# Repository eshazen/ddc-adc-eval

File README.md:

# ddc-adc-eval

Evaluation board for DDC112 ADC (Arduino UNO shield?).
See `led-photodiode-avr` design for working board.

## Notes from DDC112 datasheet:

* CLK freq range 1-10MHz
* Can generate 8MHz easily using AVR CTC
  <br>Conversion rate then 1.6kHz max
* It is recommended CONV toggle within ±10ns of the rising edge of CLK
* Mode (Cont vs Ncont) selected by state of CONT pin at power-up
  <br>can also switch based on T(INT): space between CONV edges > 4794 clocks
  (600uS at 8MHz clock)
* Data ready at ~526uS at 8MHz (4208 clocks)

## Readout strategy

* Readout function takes ~32us for 20 bits
* So maybe use CONV period of 558 + 10us (568us or 4544 clocks - 9088 period)

## Version 2 ECOs

### Main board

* **Address conflict** - U1 and U5 have the same address.
<br>Need to cut trace to U5-13 and wire U15-13 to U15-16
<br>This changes U5 address from 0x90 to 0x92
* [done] Add transistors, expand to support 8 LEDs
* [done] Change to common anode configuration (incl connector pinout)
* [done] Correct external caps on DDC (2 -> 4 C's)
* [done] Add 12 bit ADC for temperature sensor
* [done] Testpoints?

### Optical board

* [done] Fix photodiode pinout
* [done] Add temp sensor next to photodiode on copper pad
* [done] Add two Marubeni footprints next to D1 and D3
* [done] Wire 8 LED drivers to the 9 LEDs with a jumper to choose between e.g. D3 and one Marubeni channel.
* [done] Change to common anode topology
*

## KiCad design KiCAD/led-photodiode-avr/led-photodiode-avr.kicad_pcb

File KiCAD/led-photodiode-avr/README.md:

# led-photodiode-avr

This is a test board with a 3-channel constant-current LED driver,
two-channel DDC112 ADC and an ATMega328 MCU.

An interactive CLI for testing is available in
`software/avr-clock-test`.

## Testing

Board#1 is in Lina's hands

Board#2 stuffing

* C1, C15 MIA so installed 0.47uF in place of 0.33uF

Running now.

T = 9800 works well

## ECOs

Rev 2 layout completed.  See top-level README for change details.

DigiKey card for (3) sets:  https://www.digikey.com/short/bnw3t94d

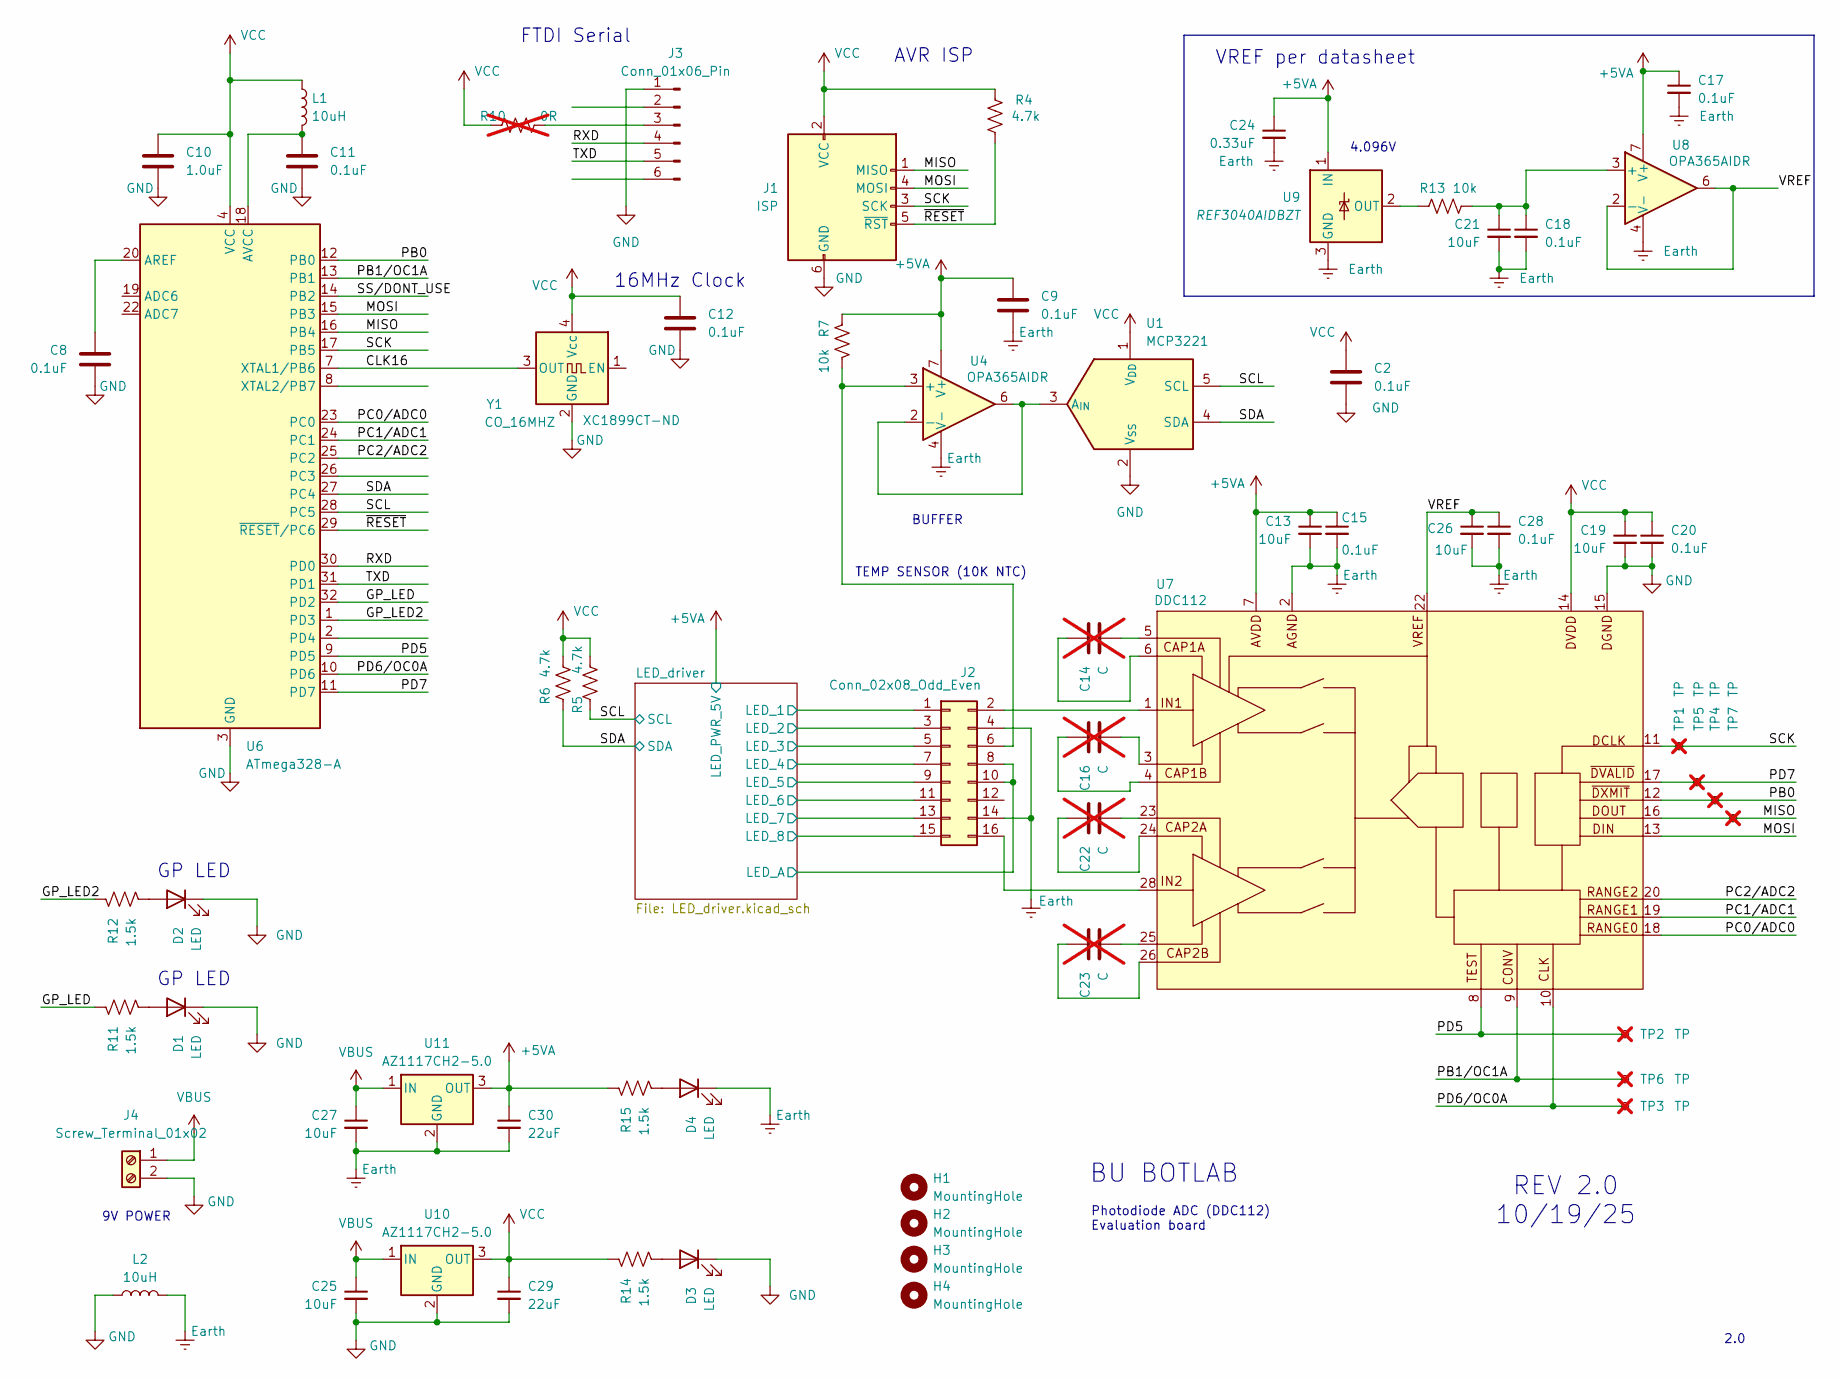
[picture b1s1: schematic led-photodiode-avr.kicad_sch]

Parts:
C2, C8, C9, C11, C12, C15, C17, C18, C20, C28: 0.1uF; C_0805_2012Metric_Pad1.18x1.45mm_HandSolder; DigikeyNumber 478-KGM21NR71H104KTCT-ND
C10: 1.0uF; C_0805_2012Metric_Pad1.18x1.45mm_HandSolder; DigikeyNumber 1276-1029-1-ND
C13, C19, C21, C25, C26, C27: 10uF; C_0805_2012Metric_Pad1.18x1.45mm_HandSolder; DigikeyNumber 1292-0805X106K250CT-ND
C14, C16, C22, C23: C; C_0603_1608Metric_Pad1.08x0.95mm_HandSolder; not fitted
C24: 0.33uF; C_0805_2012Metric_Pad1.18x1.45mm_HandSolder; DigikeyNumber 1276-1123-1-ND
C29, C30: 22uF; C_0805_2012Metric_Pad1.18x1.45mm_HandSolder; DigikeyNumber 1276-CL21A226MAYNNNECT-ND
D1, D2, D3, D4: LED; LED_0805_2012Metric_Pad1.15x1.40mm_HandSolder; DigikeyNumber 1516-QBLP631-R3ACT-ND
H1, H2, H3, H4: MountingHole; MountingHole_4.3mm_M4_DIN965_Pad
J1: ISP; IDC-Header_2x03_P2.54mm_Horizontal; DigikeyNumber 952-2092-ND
J2: Conn_02x08_Odd_Even; PinHeader_2x08_P2.54mm_Vertical; DigikeyNumber 10129381-916001BLF-ND
J3: Conn_01x06_Pin; PinHeader_1x06_P2.54mm_Horizontal; DigikeyNumber 2057-PH1RB-06-UA-ND
J4: Screw_Terminal_01x02; TerminalBlock_MaiXu_MX126-5.0-02P_1x02_P5.00mm; DigikeyNumber A98076-ND
L1, L2: 10uH; L_0805_2012Metric_Pad1.15x1.40mm_HandSolder; DigikeyNumber 445-6762-1-ND
R4, R5, R6: 4.7k; R_0805_2012Metric_Pad1.20x1.40mm_HandSolder; DigikeyNumber 541-4131-1-ND
R7, R13: 10k; R_0805_2012Metric_Pad1.20x1.40mm_HandSolder; DigikeyNumber P10KACT-ND
R10: 0R; R_0805_2012Metric_Pad1.20x1.40mm_HandSolder; not fitted
R11, R12, R14, R15: 1.5k; R_0805_2012Metric_Pad1.20x1.40mm_HandSolder; DigikeyNumber 541-4161-1-ND
TP1, TP2, TP3, TP4, TP5, TP6, TP7: TP; TestPoint_Pad_D1.0mm; not fitted
U1: MCP3221; SOT-23-5; DigikeyNumber MCP3221A0T-E/OTCT-ND
U4, U8: OPA365AIDR; SOIC-8_3.9x4.9mm_P1.27mm; DigikeyNumber 296-46162-1-ND
U6: ATmega328-A; TQFP-32_7x7mm_P0.8mm; DigikeyNumber ATMEGA328P-AU-ND
U7: DDC112; SOIC-28W_7.5x17.9mm_P1.27mm; DigikeyNumber 296-DDC112U/1KCT-ND
U9: REF3040AIDBZT; SOT-23; DigikeyNumber REF3040AIDBZTCT-ND
U10, U11: AZ1117CH2-5.0; SOT-223-3_TabPin2; DigikeyNumber 31-AZ1117CH2-5.0TRG1CT-ND
Y1: CO_16MHZ; Oscillator_SMD_Abracon_ASE-4Pin_3.2x2.5mm; DigikeyNumber XC1899CT-ND

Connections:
+5VA: C9.1, C13.1, C15.1, C17.1, C24.1, C30.1, J2.8, J2.10, R7.1, R15.1, U4.7 (V+), U7.7 (AVDD), U8.7 (V+), U9.1 (IN), U11.3 (OUT); also elsewhere on the board
/CLK16: U6.7 (XTAL1/PB6), Y1.3 (OUT)
/GP_LED: R11.1, U6.32 (PD2)
/GP_LED2: R12.1, U6.1 (PD3)
/LED_driver/LED_1: J2.1; also elsewhere on the board
/LED_driver/LED_2: J2.3; also elsewhere on the board
/LED_driver/LED_3: J2.5; also elsewhere on the board
/LED_driver/LED_4: J2.7; also elsewhere on the board
/LED_driver/LED_5: J2.9; also elsewhere on the board
/LED_driver/LED_6: J2.11; also elsewhere on the board
/LED_driver/LED_7: J2.13; also elsewhere on the board
/LED_driver/LED_8: J2.15; also elsewhere on the board
/MISO: J1.1 (MISO), TP7.1, U6.16 (PB4), U7.16 (DOUT)
/MOSI: J1.4 (MOSI), U6.15 (PB3), U7.13 (DIN)
/PB0: TP4.1, U6.12 (PB0), U7.12 (~DXMIT)
/PB1/OC1A: TP6.1, U6.13 (PB1), U7.9 (CONV)
/PC0/ADC0: U6.23 (PC0), U7.18 (RANGE0)
/PC1/ADC1: U6.24 (PC1), U7.19 (RANGE1)
/PC2/ADC2: U6.25 (PC2), U7.20 (RANGE2)
/PD5: TP2.1, U6.9 (PD5), U7.8 (TEST)
/PD6/OC0A: TP3.1, U6.10 (PD6), U7.10 (CLK)
/PD7: TP5.1, U6.11 (PD7), U7.17 (~DVALID)
/RXD: J3.4, U6.30 (PD0)
/SCK: J1.3 (SCK), TP1.1, U6.17 (PB5), U7.11 (DCLK)
/SCL: R5.1, U1.5 (SCL), U6.28 (PC5); also elsewhere on the board
/SDA: R6.1, U1.4 (SDA), U6.27 (PC4); also elsewhere on the board
/SS/DONT_USE: U6.14 (PB2)
/TXD: J3.5, U6.31 (PD1)
/VREF: C26.1, C28.1, U7.22 (VREF), U8.2 (-), U8.6
/~RESET: J1.5 (~RST), R4.1, U6.29 (~RESET/PC6)
Earth: C9.2, C13.2, C15.2, C17.2, C18.2, C21.2, C24.2, C26.2, C27.2, C28.2, C30.2, D4.1 (K), J2.4, J2.14, L2.2, U4.4 (V-), U7.2 (AGND), U7.21 (AGND), U7.27 (AGND), U8.4 (V-), U9.3 (GND), U11.2 (GND); also elsewhere on the board
GND: C2.2, C8.2, C10.2, C11.2, C12.2, C19.2, C20.2, C25.2, C29.2, D1.1 (K), D2.1 (K), D3.1 (K), J1.6 (GND), J3.1, J4.2, L2.1, U1.2 (V_{SS}), U6.3 (GND), U6.5 (GND), U6.21 (GND), U7.15 (DGND), U10.2 (GND), Y1.2 (GND); also elsewhere on the board
unnamed: C14.1, U7.6 (CAP1A)
unnamed: C14.2, U7.5 (CAP1A)
unnamed: C16.1, U7.4 (CAP1B)
unnamed: C16.2, U7.3 (CAP1B)
unnamed: C22.1, U7.24 (CAP2A)
unnamed: C22.2, U7.23 (CAP2A)
unnamed: C23.1, U7.26 (CAP2B)
unnamed: C23.2, U7.25 (CAP2B)
unnamed: D1.2 (A), R11.2
unnamed: D2.2 (A), R12.2
unnamed: D3.2 (A), R14.2
unnamed: D4.2 (A), R15.2
unnamed: J2.2, U7.1 (IN1)
unnamed: J2.6, R7.2, U4.3 (+)
unnamed: J2.16, U7.28 (IN2)
unnamed: J3.3, R10.2
unnamed: U1.3 (A_{IN}), U4.2 (-), U4.6
unnamed: C8.1, U6.20 (AREF)
unnamed: C11.1, L1.2, U6.18 (AVCC)
unnamed: C18.1, C21.1, R13.2, U8.3 (+)
unnamed: R13.1, U9.2 (OUT)
VBUS: C25.1, C27.1, J4.1, U10.1 (IN), U11.1 (IN)
VCC: C2.1, C10.1, C12.1, C19.1, C20.1, C29.1, J1.2 (VCC), L1.1, R4.2, R5.2, R6.2, R10.1, R14.1, U1.1 (V_{DD}), U6.4 (VCC), U6.6 (VCC), U7.14 (DVDD), U10.3 (OUT), Y1.4 (Vcc); also elsewhere on the board

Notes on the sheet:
BUFFER
REV 2.0 10/19/25
AVR ISP
FTDI Serial
4.096V
2.0
GP LED
VREF per datasheet
9V POWER
BU BOTLAB
TEMP SENSOR (10K NTC)
16MHz Clock
Photodiode ADC (DDC112) Evaluation board

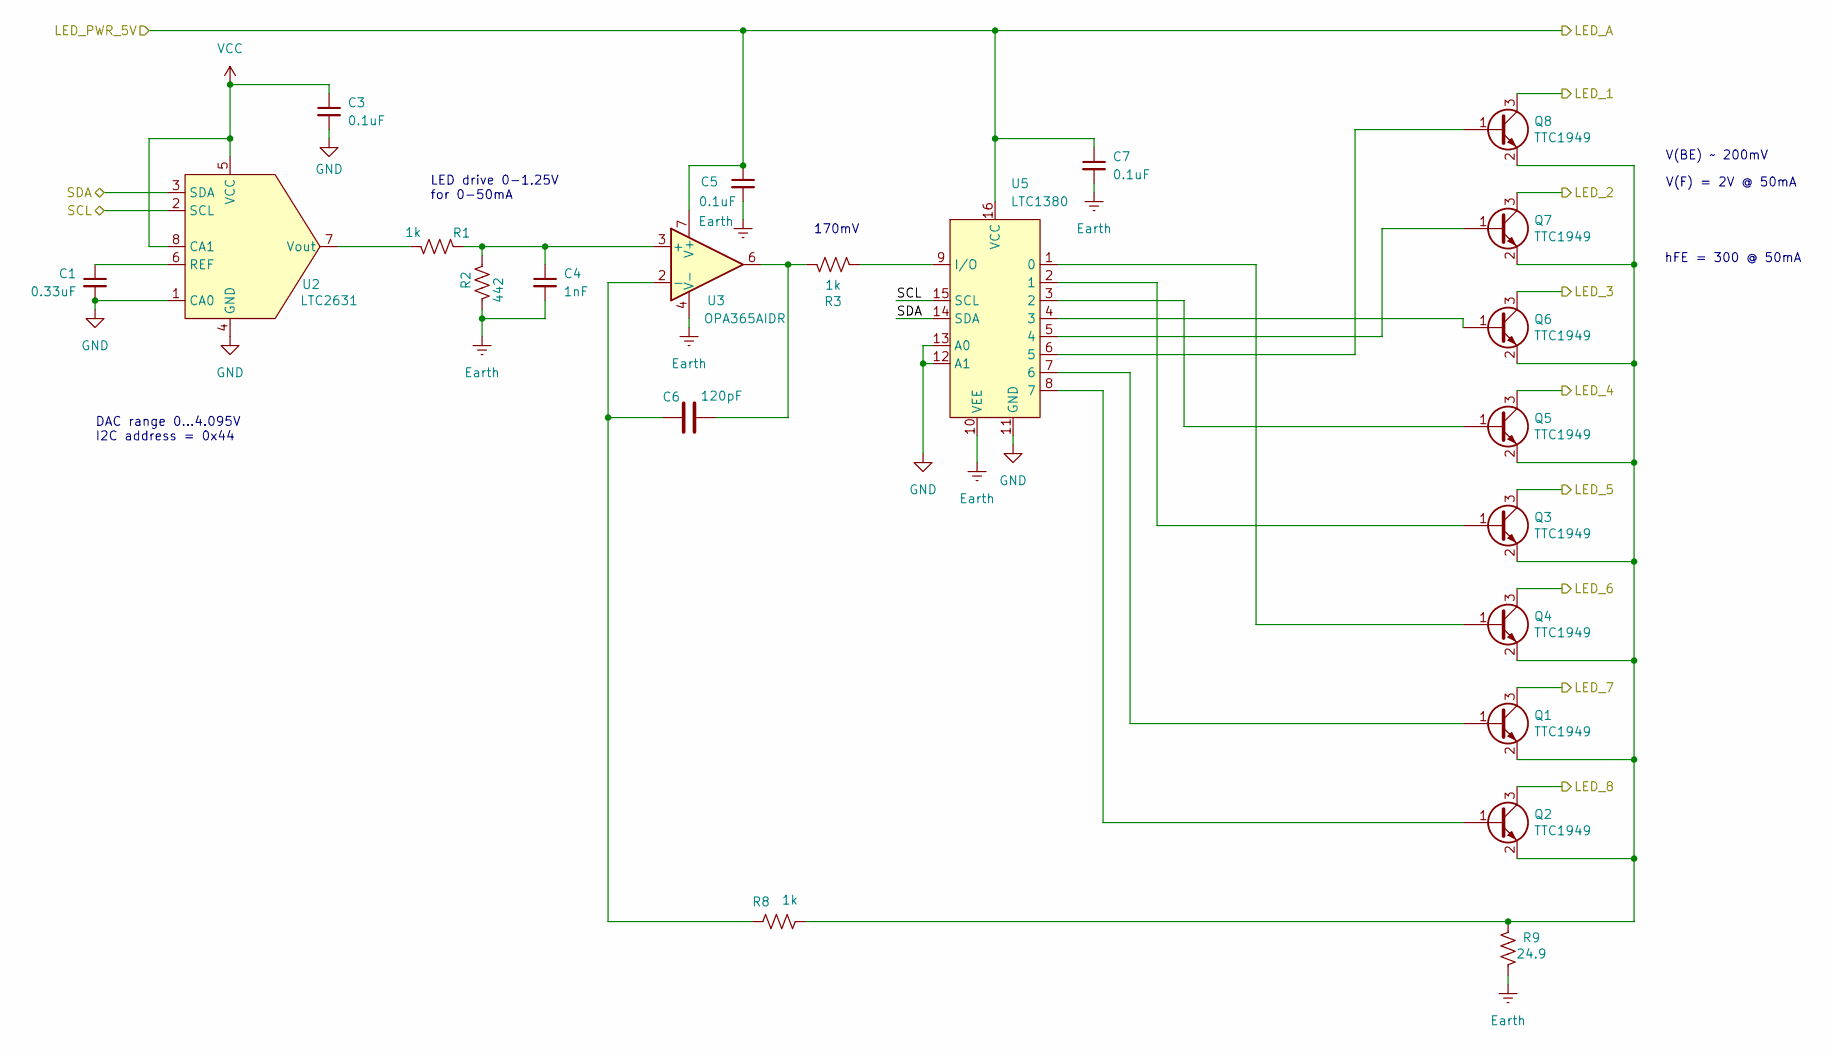
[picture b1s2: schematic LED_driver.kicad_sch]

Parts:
C1: 0.33uF; C_0805_2012Metric_Pad1.18x1.45mm_HandSolder; DigikeyNumber 1276-1123-1-ND
C3, C5, C7: 0.1uF; C_0805_2012Metric_Pad1.18x1.45mm_HandSolder; DigikeyNumber 478-KGM21NR71H104KTCT-ND
C4: 1nF; C_0805_2012Metric_Pad1.18x1.45mm_HandSolder; DigikeyNumber 399-C0805C102J5GACTUCT-ND
C6: 120pF; C_0805_2012Metric_Pad1.18x1.45mm_HandSolder; DigikeyNumber 399-C0805C121J3GACTUCT-ND
Q1, Q2, Q3, Q4, Q5, Q6, Q7, Q8: TTC1949; SC-59; DigikeyNumber TTC1949-GRLFCT-ND
R1, R3, R8: 1k; R_0805_2012Metric_Pad1.20x1.40mm_HandSolder; DigikeyNumber 541-1.00KCCT-ND
R2: 442; R_0805_2012Metric_Pad1.20x1.40mm_HandSolder; DigikeyNumber 311-442CRCT-ND
R9: 24.9; R_1206_3216Metric; DigikeyNumber 541-CRCW120624R9FKEAHPCT-ND
U2: LTC2631; TSOT-23-8; DigikeyNumber LTC2631CTS8-HZ12#TRMPBFCT-ND
U3: OPA365AIDR; SOIC-8_3.9x4.9mm_P1.27mm; DigikeyNumber 296-46162-1-ND
U5: LTC1380; SOIC-16_3.9x9.9mm_P1.27mm; DigikeyNumber 505-LTC1380CS#PBF-ND

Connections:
+5VA: C5.1, C7.1, U3.7 (V+), U5.16 (VCC); also elsewhere on the board
/LED_driver/LED_1: Q8.3 (C); also elsewhere on the board
/LED_driver/LED_2: Q7.3 (C); also elsewhere on the board
/LED_driver/LED_3: Q6.3 (C); also elsewhere on the board
/LED_driver/LED_4: Q5.3 (C); also elsewhere on the board
/LED_driver/LED_5: Q3.3 (C); also elsewhere on the board
/LED_driver/LED_6: Q4.3 (C); also elsewhere on the board
/LED_driver/LED_7: Q1.3 (C); also elsewhere on the board
/LED_driver/LED_8: Q2.3 (C); also elsewhere on the board
/SCL: U2.2 (SCL), U5.15 (SCL); also elsewhere on the board
/SDA: U2.3 (SDA), U5.14 (SDA); also elsewhere on the board
Earth: C4.2, C5.2, C7.2, R2.2, R9.1, U3.4 (V-), U5.10 (VEE); also elsewhere on the board
GND: C1.2, C3.2, U2.1 (CA0), U2.4 (GND), U5.11 (GND), U5.12 (A1), U5.13 (A0); also elsewhere on the board
unnamed: C6.2, R3.2, U3.6
unnamed: Q1.1 (B), U5.7 (6)
unnamed: Q1.2 (E), Q2.2 (E), Q3.2 (E), Q4.2 (E), Q5.2 (E), Q6.2 (E), Q7.2 (E), Q8.2 (E), R8.1, R9.2
unnamed: Q2.1 (B), U5.8 (7)
unnamed: Q3.1 (B), U5.2 (1)
unnamed: Q4.1 (B), U5.1 (0)
unnamed: Q5.1 (B), U5.3 (2)
unnamed: Q6.1 (B), U5.4 (3)
unnamed: Q7.1 (B), U5.5 (4)
unnamed: Q8.1 (B), U5.6 (5)
unnamed: C1.1, U2.6 (REF)
unnamed: R1.2, U2.7 (Vout)
unnamed: C4.1, R1.1, R2.1, U3.3 (+)
unnamed: C6.1, R8.2, U3.2 (-)
unnamed: R3.1, U5.9 (I/O)
VCC: C3.1, U2.5 (VCC), U2.8 (CA1); also elsewhere on the board

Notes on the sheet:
DAC range 0...4.095V I2C address = 0x44
LED drive 0-1.25V for 0-50mA
V(BE) ~ 200mV
170mV
V(F) = 2V @ 50mA
hFE = 300 @ 50mA

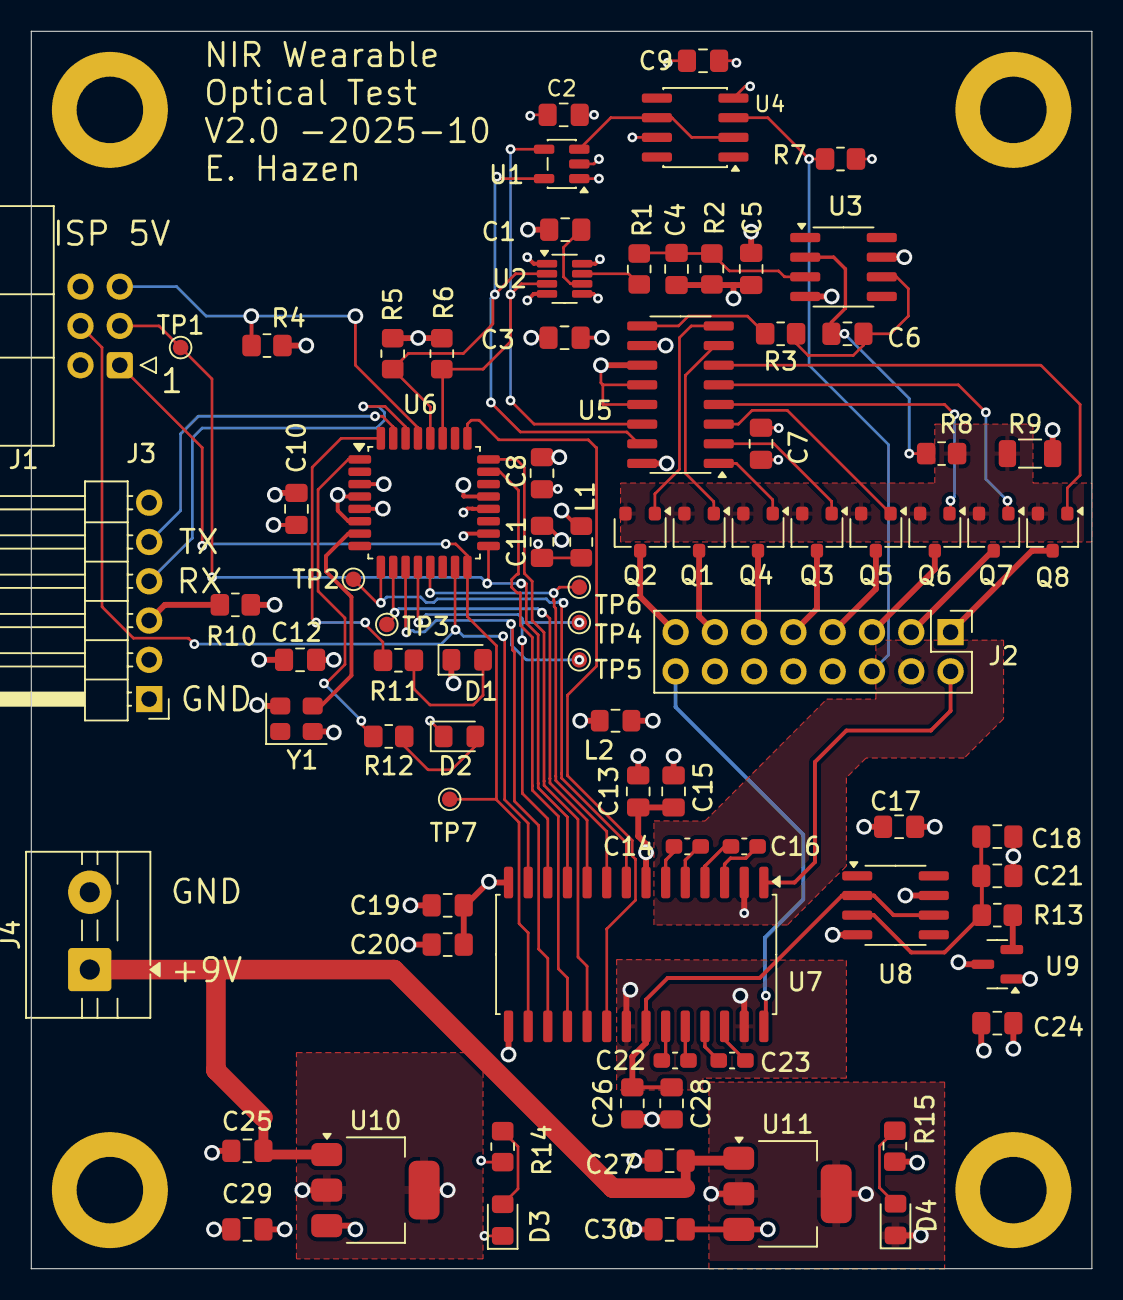
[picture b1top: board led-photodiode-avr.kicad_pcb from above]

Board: 4 copper layers, 68.6 x 80.0 mm, 86 parts (0 on the bottom side), 69 nets.

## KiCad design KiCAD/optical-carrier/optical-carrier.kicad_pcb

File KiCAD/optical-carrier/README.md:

# optical-carrier

Simple carrier board for one photodiode, 3 discrete
and two 3-wavelength LEDs.

## ECOs

Rev 2 layout completed.  See top-level README for details.

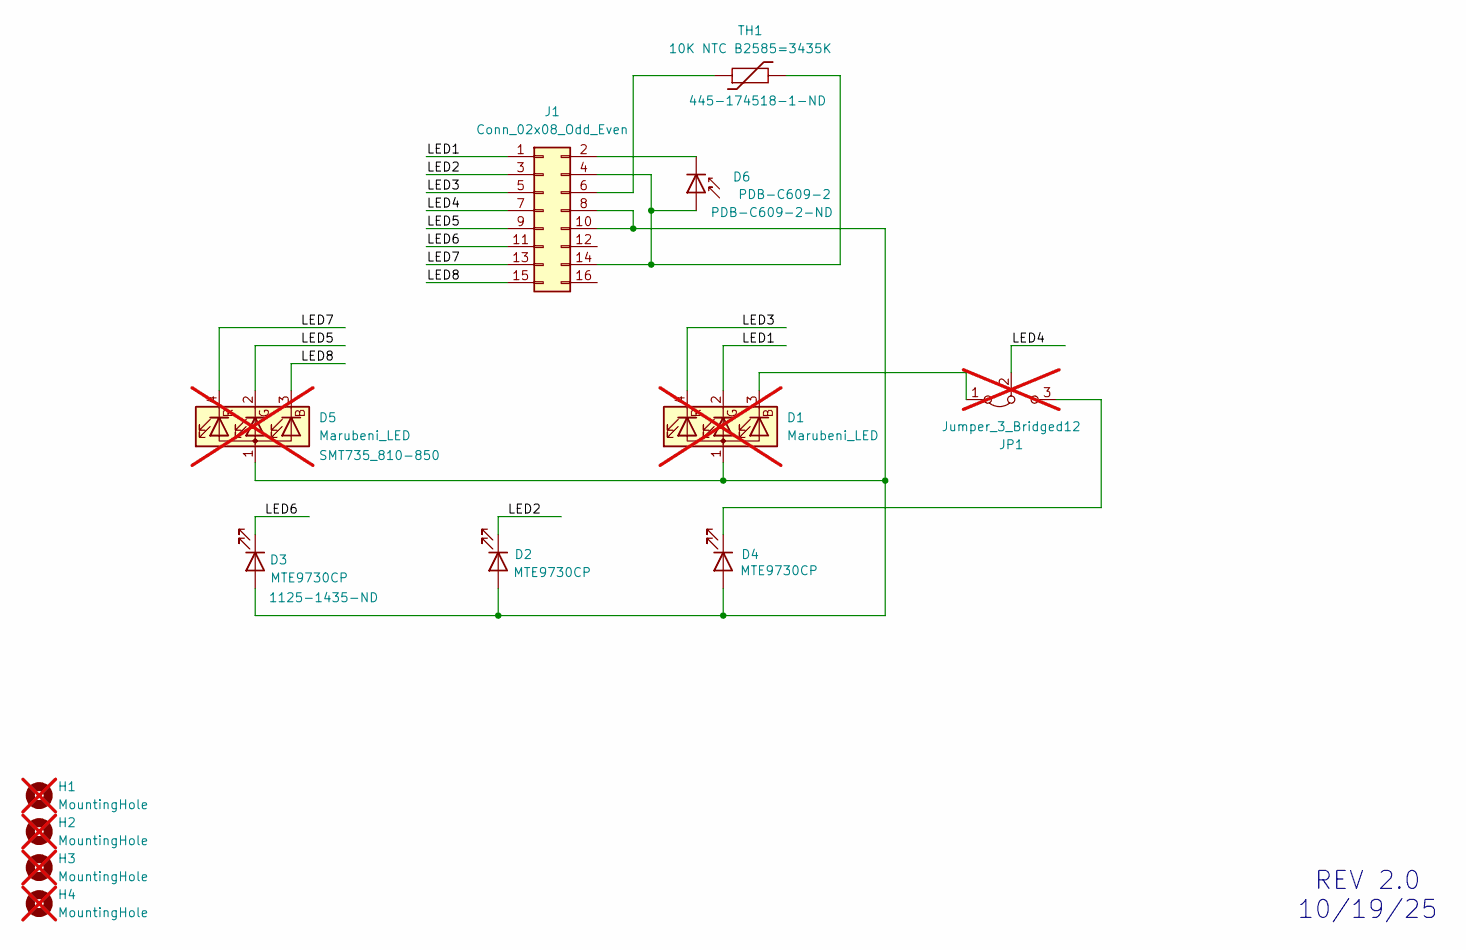
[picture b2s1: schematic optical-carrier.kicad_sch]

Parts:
D1, D5: Marubeni_LED; Marubeni; not fitted
D2, D3, D4: MTE9730CP; MTE9730
D6: PDB-C609-2
H1, H2, H3, H4: MountingHole; MountingHole_4.3mm_M4_DIN965; not fitted
J1: Conn_02x08_Odd_Even; PinSocket_2x08_P2.54mm_Vertical
JP1: Jumper_3_Bridged12; PinHeader_1x03_P2.54mm_Vertical; not fitted
TH1: 10K NTC B2585=3435K; R_0603_1608Metric_Pad0.98x0.95mm_HandSolder

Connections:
/LED1: D1.2 (GK), J1.1
/LED2: D2.1 (K), J1.3
/LED3: D1.4 (RK), J1.5
/LED4: J1.7, JP1.2 (C)
/LED5: D5.2 (GK), J1.9
/LED6: D3.1 (K), J1.11
/LED7: D5.4 (RK), J1.13
/LED8: D5.3 (BK), J1.15
unnamed: D1.1 (A), D2.2 (A), D3.2 (A), D4.2 (A), D5.1 (A), J1.8, J1.10
unnamed: D1.3 (BK), JP1.1 (A)
unnamed: D4.1 (K), JP1.3 (B)
unnamed: D6.2 (A), J1.4, J1.14, TH1.2
unnamed: D6.1 (K), J1.2
unnamed: J1.6, TH1.1

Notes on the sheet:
REV 2.0 10/19/25

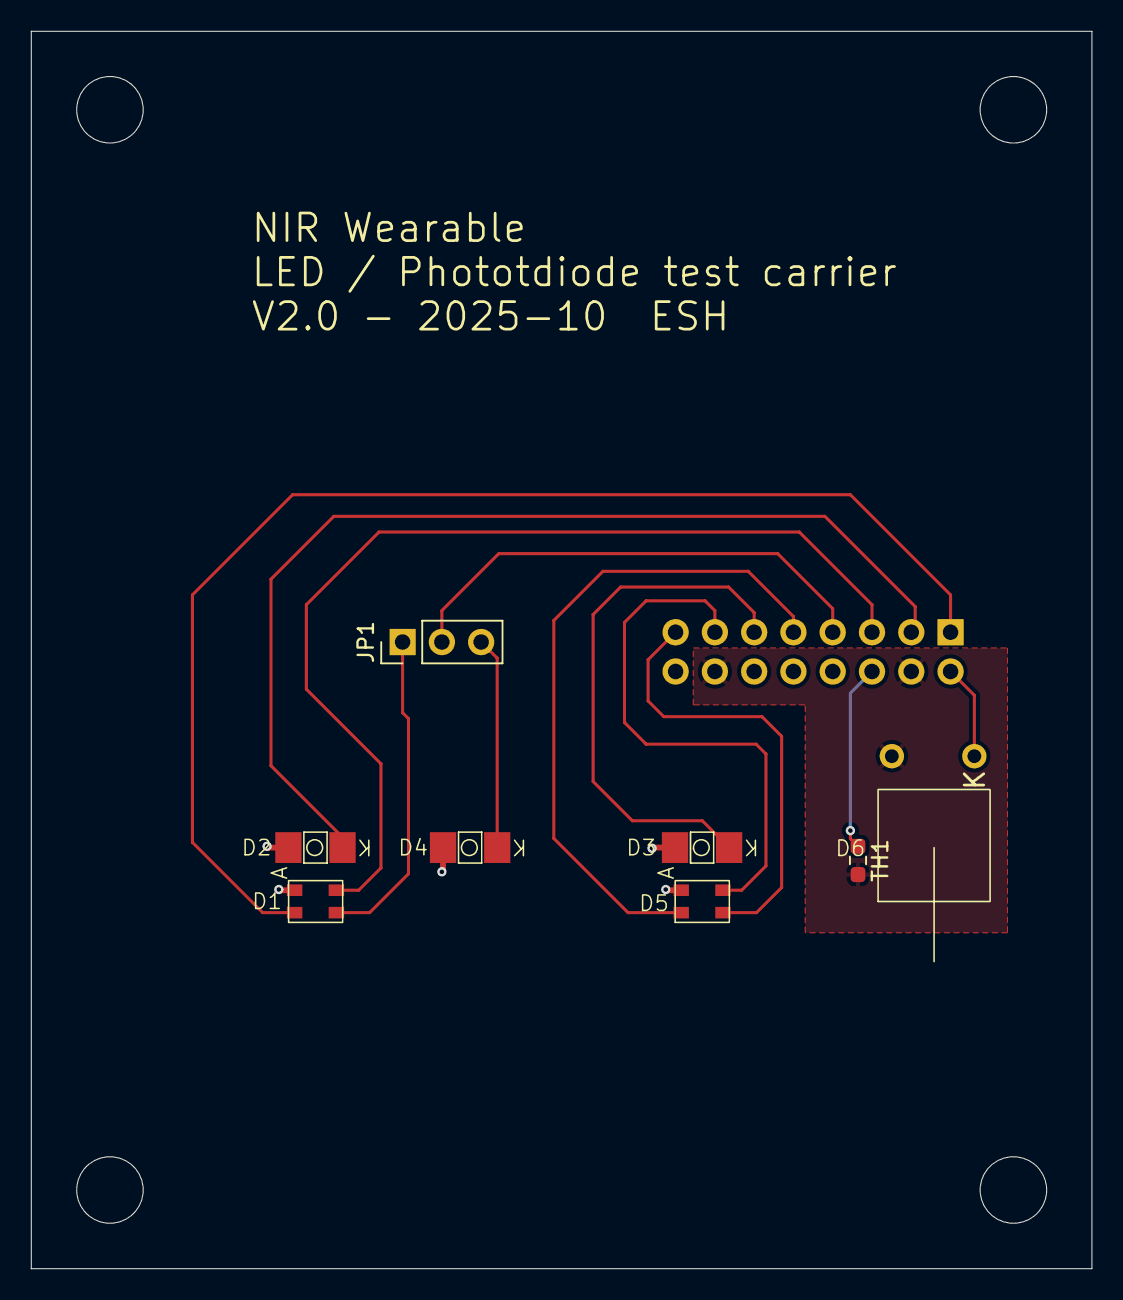
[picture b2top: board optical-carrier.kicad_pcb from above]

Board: 2 copper layers, 68.6 x 80.0 mm, 13 parts (1 on the bottom side), 14 nets.

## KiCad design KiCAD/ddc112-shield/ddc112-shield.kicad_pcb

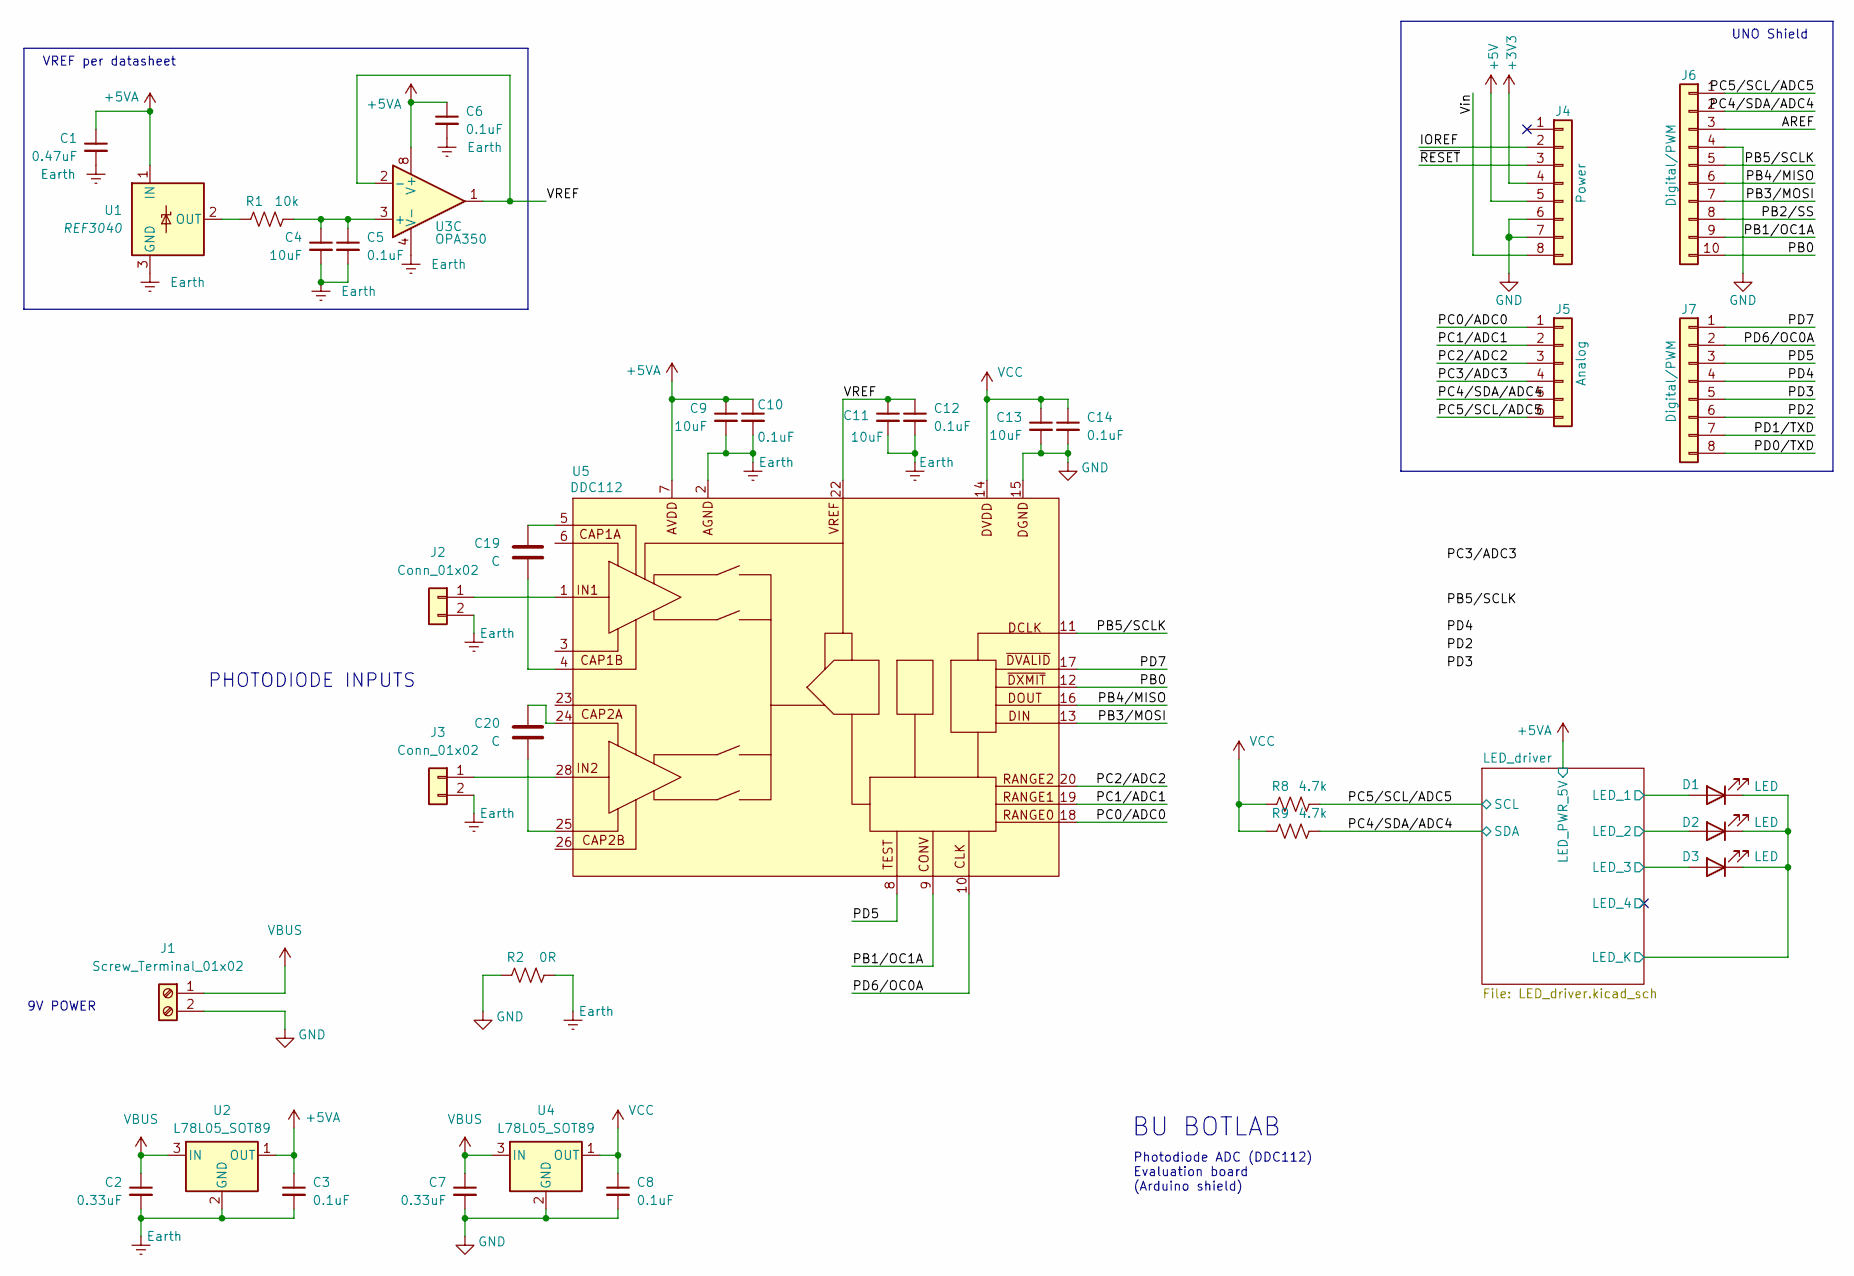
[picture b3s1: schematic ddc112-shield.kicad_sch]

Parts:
C1: 0.47uF; C_0805_2012Metric_Pad1.18x1.45mm_HandSolder
C2, C7: 0.33uF; C_0805_2012Metric_Pad1.18x1.45mm_HandSolder
C3, C5, C6, C8, C10, C12, C14: 0.1uF; C_0805_2012Metric_Pad1.18x1.45mm_HandSolder
C4, C9, C11, C13: 10uF; C_0805_2012Metric_Pad1.18x1.45mm_HandSolder
C19, C20: C; C_0805_2012Metric_Pad1.18x1.45mm_HandSolder
D1, D2, D3: LED; PinHeader_1x02_P2.54mm_Vertical
J1: Screw_Terminal_01x02; TerminalBlock_MaiXu_MX126-5.0-02P_1x02_P5.00mm
J2, J3: Conn_01x02; PinHeader_1x02_P2.54mm_Vertical
J4: Power; PinSocket_1x08_P2.54mm_Vertical
J5: Analog; PinSocket_1x06_P2.54mm_Vertical
J6: Digital/PWM; PinSocket_1x10_P2.54mm_Vertical
J7: Digital/PWM; PinSocket_1x08_P2.54mm_Vertical
R1: 10k; R_0805_2012Metric_Pad1.20x1.40mm_HandSolder
R2: 0R; R_0805_2012Metric_Pad1.20x1.40mm_HandSolder
R8, R9: 4.7k; R_0805_2012Metric_Pad1.20x1.40mm_HandSolder
U1: REF3040; SOT-23
U2, U4: L78L05_SOT89; SOT-89-3
U3: OPA350; SOIC-8_3.9x4.9mm_P1.27mm
U5: DDC112; SOIC-28W_7.5x17.9mm_P1.27mm

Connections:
+3V3: J4.4
+5V: J4.5
/AREF: J6.3
/IOREF: J4.2
/LED_driver/LED_1: D1.2 (A); also elsewhere on the board
/LED_driver/LED_2: D2.2 (A); also elsewhere on the board
/LED_driver/LED_3: D3.2 (A); also elsewhere on the board
/LED_driver/LED_K: D1.1 (K), D2.1 (K), D3.1 (K); also elsewhere on the board
/PB0: J6.10, U5.12 (~DXMIT)
/PB1/OC1A: J6.9, U5.9 (CONV)
/PB2/SS: J6.8
/PB3/MOSI: J6.7, U5.13 (DIN)
/PB4/MISO: J6.6, U5.16 (DOUT)
/PB5/SCLK: J6.5, U5.11 (DCLK)
/PC0/ADC0: J5.1, U5.18 (RANGE0)
/PC1/ADC1: J5.2, U5.19 (RANGE1)
/PC2/ADC2: J5.3, U5.20 (RANGE2)
/PC3/ADC3: J5.4
/PC4/SDA/ADC4: J5.5, J6.2, R9.2; also elsewhere on the board
/PC5/SCL/ADC5: J5.6, J6.1, R8.2; also elsewhere on the board
/PD0/TXD: J7.8
/PD1/TXD: J7.7
/PD2: J7.6
/PD3: J7.5
/PD4: J7.4
/PD5: J7.3, U5.8 (TEST)
/PD6/OC0A: J7.2, U5.10 (CLK)
/PD7: J7.1, U5.17 (~DVALID)
/VREF: C11.1, C12.1, U3.1, U3.2 (-), U5.22 (VREF)
/Vin: J4.8
/~RESET: J4.3
GND: C7.2, C8.2, C13.2, C14.2, J1.2, J4.6, J4.7, J6.4, R2.1, U4.2 (GND), U5.15 (DGND); also elsewhere on the board
unnamed: C19.1, U5.5 (CAP1A)
unnamed: C19.2, U5.4 (CAP1B)
unnamed: C20.1, U5.24 (CAP2A)
unnamed: C20.2, U5.25 (CAP2B)
unnamed: J2.1, U5.1 (IN1)
unnamed: J3.1, U5.28 (IN2)
unnamed: R1.1, U1.2 (OUT)
unnamed: C4.1, C5.1, R1.2, U3.3 (+)
VBUS: C2.1, C7.1, J1.1, U2.3 (IN), U4.3 (IN)
VCC: C8.1, C13.1, C14.1, R8.1, R9.1, U4.1 (OUT), U5.14 (DVDD)

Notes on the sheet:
PHOTODIODE INPUTS
UNO Shield
VREF per datasheet
9V POWER
BU BOTLAB
Photodiode ADC (DDC112) Evaluation board (Arduino shield)

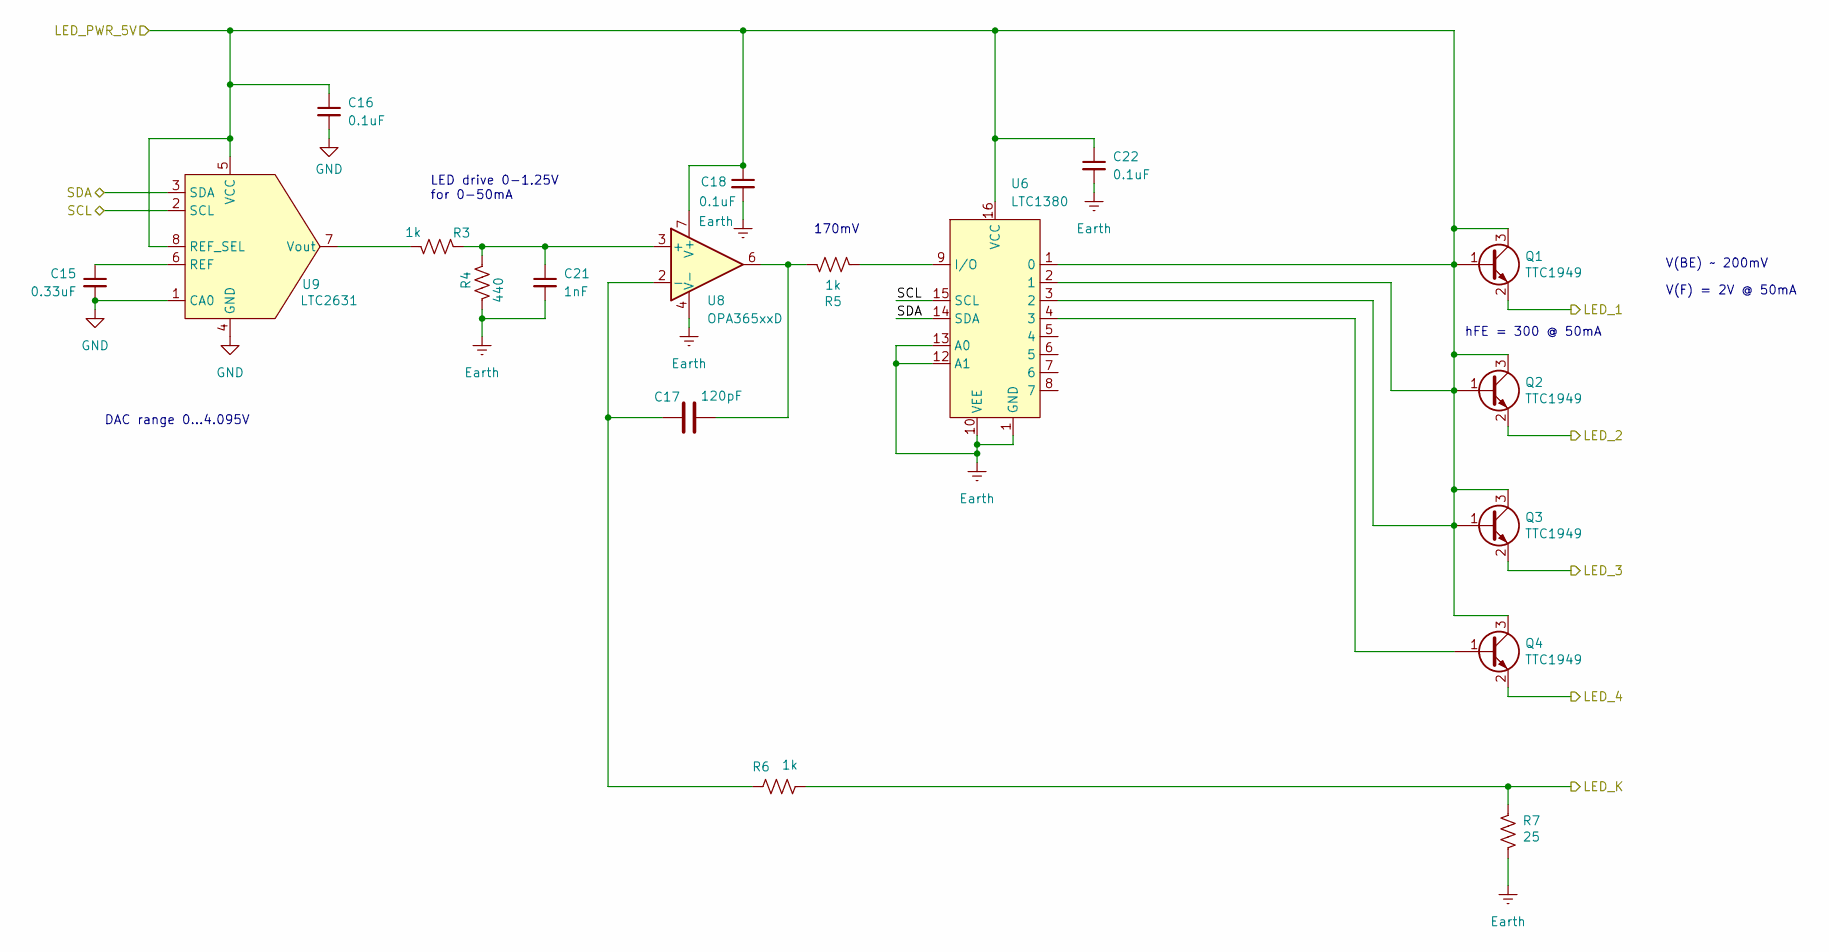
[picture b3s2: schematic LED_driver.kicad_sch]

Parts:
C15: 0.33uF; C_0805_2012Metric_Pad1.18x1.45mm_HandSolder; DigikeyNumber 1276-2048-1-ND
C16, C22: 0.1uF; C_0805_2012Metric_Pad1.18x1.45mm_HandSolder; DigikeyNumber 1276-1005-1-ND
C17: 120pF; C_0805_2012Metric_Pad1.18x1.45mm_HandSolder
C18: 0.1uF; C_0805_2012Metric_Pad1.18x1.45mm_HandSolder
C21: 1nF; C_0805_2012Metric_Pad1.18x1.45mm_HandSolder
Q1, Q2, Q3, Q4: TTC1949; SC-59; DigikeyNumber TTC1949-GRLFCT-ND
R3, R5, R6: 1k; R_0805_2012Metric_Pad1.20x1.40mm_HandSolder
R4: 440; R_0805_2012Metric_Pad1.20x1.40mm_HandSolder
R7: 25; R_1206_3216Metric
U6: LTC1380; SOIC-16_3.9x9.9mm_P1.27mm; DigikeyNumber 505-LTC1380CS#PBF-ND
U8: OPA365xxD; SOIC-8_3.9x4.9mm_P1.27mm
U9: LTC2631; TSOT-23-8; DigikeyNumber LTC2631CTS8-HZ12#TRMPBFCT-ND

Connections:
/LED_driver/LED_1: Q1.2 (E); also elsewhere on the board
/LED_driver/LED_2: Q2.2 (E); also elsewhere on the board
/LED_driver/LED_3: Q3.2 (E); also elsewhere on the board
/LED_driver/LED_4: Q4.2 (E)
/LED_driver/LED_K: R6.1, R7.2; also elsewhere on the board
/PC4/SDA/ADC4: U6.14 (SDA), U9.3 (SDA); also elsewhere on the board
/PC5/SCL/ADC5: U6.15 (SCL), U9.2 (SCL); also elsewhere on the board
GND: C15.2, C16.2, U9.1 (CA0), U9.4 (GND); also elsewhere on the board
unnamed: C17.2, R5.2, U8.6
unnamed: Q4.1 (B), U6.4 (3)
unnamed: R5.1, U6.9 (I/O)
unnamed: C21.1, R3.1, R4.1, U8.3 (+)
unnamed: C17.1, R6.2, U8.2 (-)
unnamed: C15.1, U9.6 (REF)
unnamed: R3.2, U9.7 (Vout)

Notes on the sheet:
DAC range 0...4.095V
LED drive 0-1.25V for 0-50mA
V(BE) ~ 200mV
170mV
V(F) = 2V @ 50mA
hFE = 300 @ 50mA

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
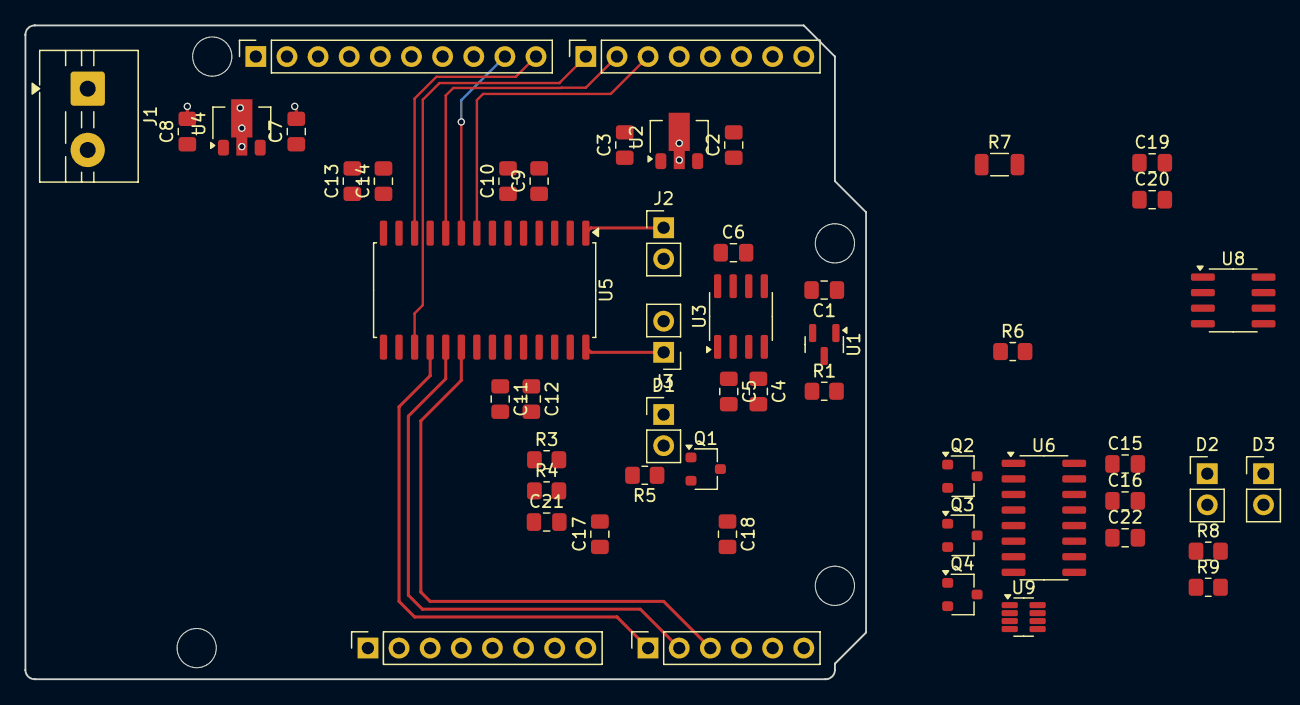
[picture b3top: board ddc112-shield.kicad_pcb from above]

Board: 4 copper layers, 68.6 x 53.3 mm, 57 parts (1 on the bottom side), 38 nets.

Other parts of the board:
MH1, MH2, MH3, MH4: MountingHole_3.2mm

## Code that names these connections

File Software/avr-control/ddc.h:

#ifndef DDC_H_INCLUDED
#define DDC_H_INCLUDED

#define DCLK_PORT PORTB
#define DCLK_DDR DDRB
#define DCLK_PIN PINB

#define DCLK_BIT PB5
#define DIN_BIT PB3
#define DOUT_BIT PB4
#define DXMIT_BIT PB0
#define CONV_BIT PB1

#define DVALID_PORT PORTD
#define DVALID_DDR DDRD
#define DVALID_PIN PIND
#define DVALID_BIT PD7

#define TEST_PORT PORTD
#define TEST_DDR DDRD
#define TEST_PIN PIND
#define TEST_BIT PD5
#define TEST_MASK _BV(TEST_BIT)

#define RANGE_PORT PORTC
#define RANGE_DDR DDRC
#define RANGE_MASK 7

#ifdef UNO_TARGET
#define LED_PORT PORTB
#define LED_DDR DDRB
#define LED_BIT PB5
#define LED_MASK _BV(LED_BIT)
#endif

#ifdef AVR_TARGET
#define LED_PORT PORTD
#define LED_DDR DDRD
#define LED_MASK (_BV(PD2)|_BV(PD3))
#define LED_BIT PD2
#define LED2_BIT PD3
#endif

void ddc_init();
void ddc_range(uint8_t r);
void ddc_leds(uint8_t v);
int wait_for_dvalid();
int wait_for_dvalid_conv();
uint32_t* read_ddc();

#endif

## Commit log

2025-08-06 starting on schematic
2025-08-06 working on schematic
2025-08-06 initial schematic; test software
2025-08-06 placement adjust
2025-08-14 starting on LED driver
2025-08-15 woring on LED driver
2025-08-15 LED driver schematic complete?
2025-08-16 placement
2025-08-16 working on BOM
2025-08-16 many schematic tweaks; add fields for BOM
2025-08-16 routing done
2025-08-17 ready for review
2025-08-17 ready for review (update PDF, gerber)
2025-08-17 add 3D models, optical board
2025-08-18 small tweaks
2025-08-25 V1.0 as built
2025-08-25 readout software test
2025-08-26 update LED command and add range command
2025-08-26 Add DAC, MUX support via I2C
2025-09-02 Update PDFs
2025-09-10 DAC and MUX working, LED output OK
2025-09-11 readout working
2025-09-18 update some readmes
2025-10-01 Speed up the readout and add fast capture
2025-10-02 working average no interrupts
2025-10-02 Interrupt driven Tx and averaging in 'avr-control'
2025-10-14 more tests
2025-10-15 Add temperature readout
2025-10-16 rev 2 plans
2025-10-16 branch for V2
2025-10-16 starting on V2
2025-10-17 working on main board changes, schem done
2025-10-17 working on v2 layout
2025-10-18 routing done?
2025-10-18 update schem PDF, readmes
2025-10-18 Add op-amp buffer on temp sensor
2025-10-18 update sch PDF, renumber all refs, update all BOM fields
2025-10-19 Rev 2.0 for review
2025-10-21 hopefully final Rev 2
2025-11-19 Add support for new 12-bit thermistor readout
